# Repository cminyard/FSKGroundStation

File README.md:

# FSKGroundStation

This is a hardware design for a low-cost PacSat satellite ground
station, but it is also general two-way FSK commmunication for the 2
meter and 70 centimeter bands.  It should be possible to build these
in the US $60 range in quantity.  It can do FSK variants ([G]MSK,
[G]FSK, OOK, ASK).  Notably, it cannot do AFSK, the normal 1200bps
communication used over FM radios.

Basically, this is two radios, one for around 136-175MHz, and one for
around 430-450MHz.  Each of these radios is a simplex two-way radio
using a basic ISM radio chip.  It then has an RF power amplifier (PA)
on the TX side to boost the power to the 4-5 watt range and an RF
switch after than to switch between transmit and receive.

The radios are TI CC1125 chips.  These are standard ISM radio chips.
However, those chips are not able to do HDLC or G3RUH 9600 as used in
standard amateur radio communication.  For that, the CC1125 can
send/receive raw FSK data out a GPIO port.  A Lattice ICE40LP1K FPGA
processes the FSK to be able to do HDLC and whitening per G3RUH.

These chips are controlled by a TI CC27x5 processor over SPI.  Also,
this is designed to have enough capability to run as a stand-alone
application, like for a balloon, fox, control device, or something of
that nature.

## Host Communication

Communication with the host is through a MSPM0G5187 processor that has
USB.  It has a SPI connection to the main processor.

There is also a 2.4GHz radio on the CC27x5 processor, so a bluetooth
connection could be done.

## RF Connections

RF input/output is through SMA connectors on the end of the board.
One connector is for 2 meters only, one is for 70cm only, and one has
a diplexer on it and can be used with a dual-band antenna.  You lose
about 1dB in the diplexer, so it's slightly better to have two
antennas.

There are two open-collector (open drain, really) outputs on a 3.5mm
audio-type jack that the CPU can drive for controlling external
amplifiers or for anything else, really.

Note that you really can't transmit on both bands at the same time.
Power draw would go somewhat above 4A and heat dissipation would be a
problem.  If you have a power source that can supply that it might be
ok, but it's pushing things on the heat side.

## Powering the Board

You can use either of the two USB connectors on the board to supply
power.  To use the host connector (J3), install the jumper on J8.  A
second USB connector J10 is a power-only USB connector that can be
used to power the board if the host connection cannot supply enough
current.  To use that install the J11 jumper.

There is also J25, a standard 6.0mm OD 2.5mm ID barrel connector on
the board, center pin is +5V and the outside is ground, as usual.  You
must remove the other power jumpers (J8 and J11) to use this.

All power connectors must supply at least 3A for transmit.

## Clocks

The MSPM0G5187 has a 32.768kHz clock with enough precision to handle
the USB connection.  In addition, it's internal oscillator has a high
precision resistor, so it should be good.

The 32.768kHz oscillator is output and send to the CC27x5 processor.
The CC27x5 processor has it's own 48MHz oscillator with 20ppm
precision.

The MSPM0G5187 also outputs a basic clock that is used to clock the
FPGA.

The CC1125 chips each have their own 40MHz 20ppm TXCO.

## Heat Dissipation and Measurement

The PAs produce a lot of heat.  At full power they will be dissipating
around 4 watts.  The heat mostly comes out through the bottom of the
board on a 2.5mm square copper pad under each PA.

There are a bunch of vias on the edge of the board and three
unobstructed ground planes between these vias and the PAs.  With edge
plating, this should be able to move heat from the ground planes into
the chassis from the edge.  This is experimental.

In case the edge vias and plating don't work, the 2.5mm square copper
pad under the PAs is left bare.  That way a thermally conductive pad
or a heat sink can be put on that to move heat away.

There are two thermsistors on the board, one mounted by each PA, for
measuring temperature.

## Design Variants

Lots of things can be removed if not required, which will decrease the
price and allow slight performance improvements in some cases:

* The 3.5mm external PA control jack and associated circuits can be
  removed if not necessary.

* PacSat satellites transmit on 70cm and receive on 2m, so the ground
  station for that really only has to transmit on 2m and receive on
  70cm.  The 70cm transmit circuits could be removed and the 2m
  receive circuits could be removed.  That means you can remove the RF
  switches on the, gaining about 1dB.  That, of course, makes the
  board less flexible for other purposes.
  
* The diplexer and connector can be removed if not needed.

* If only the diplexer is used, the TX and RX connectors can be removed.

* The radios can be modified to different bands up to the capabilities
  of the various parts.  The limiting factor is the bands supported by
  the radios (TI CC1312R and CC1125 chips) and the capabilities of the
  PA (Guerrilla RF GRF5604, 100-600MHz).

* The power connectors that aren't used can be removed.

## A Box

This was designed to go into a 100mm x 88mm box like:

    JIUWU Surface Drawing Split Aluminum Enclosure Project Box
	Electronic Enclosure Case for PCB Board DIY, 88x38x100mm (WHL),
	Black

on Amazon.  The actual board dimensions are 83mm x 100mm, it should
slide into the slots in the chassis, which is supposed to be 84mm
wide.

## TODO list

* Figure out how to handle heat from the PAs.

  * Screw mount on the bottom.  This would probably require putting
    the external connectors on the bottom of the board to give space
    in a box.  It would also require ventilation of some type and
    maybe a fan.
	
  * Connect a heat transfer device to the box surface.  This would
    require mounting in a box.  If you use the box referenced above,
    there is a 5.2mm gap between the bottom of the circuit board and the
    inside of the box.  I'm not sure how to conduct the head, though.

  * Wurth has some "Graphite Foam Gaskets" that have high thermal
    conductivity and are not electrically conductive, from what I can
    tell (1KV/mm dialectric strength), and not too expensive.  Laird
    has "Thermal Transfer Gaskets," which look similar.  Also
    Bergquist thermally conductive gap pads.  You could put that
    between the PA pad and the chassis.  I can't find one that's the
    right height, though, it needs to be 5.2mm.  Maybe it can be cut?
    The custom make them, but that would be expensive.

  * It would be possible to use 2oz copper on the inner and/or outer
    layers.  This will conduct a lot more heat, but limits the board
    stacks that can be used and requires some impedance adjustments.

  * The edges of the board could be plated, allowing heat transfer out
    of the edges of the board into the chassis.

* The 2m connection to the CC1312R is actually for 169MHz.  A proper
  design for 145MHz needs to be found, or it will need to be tweaked.

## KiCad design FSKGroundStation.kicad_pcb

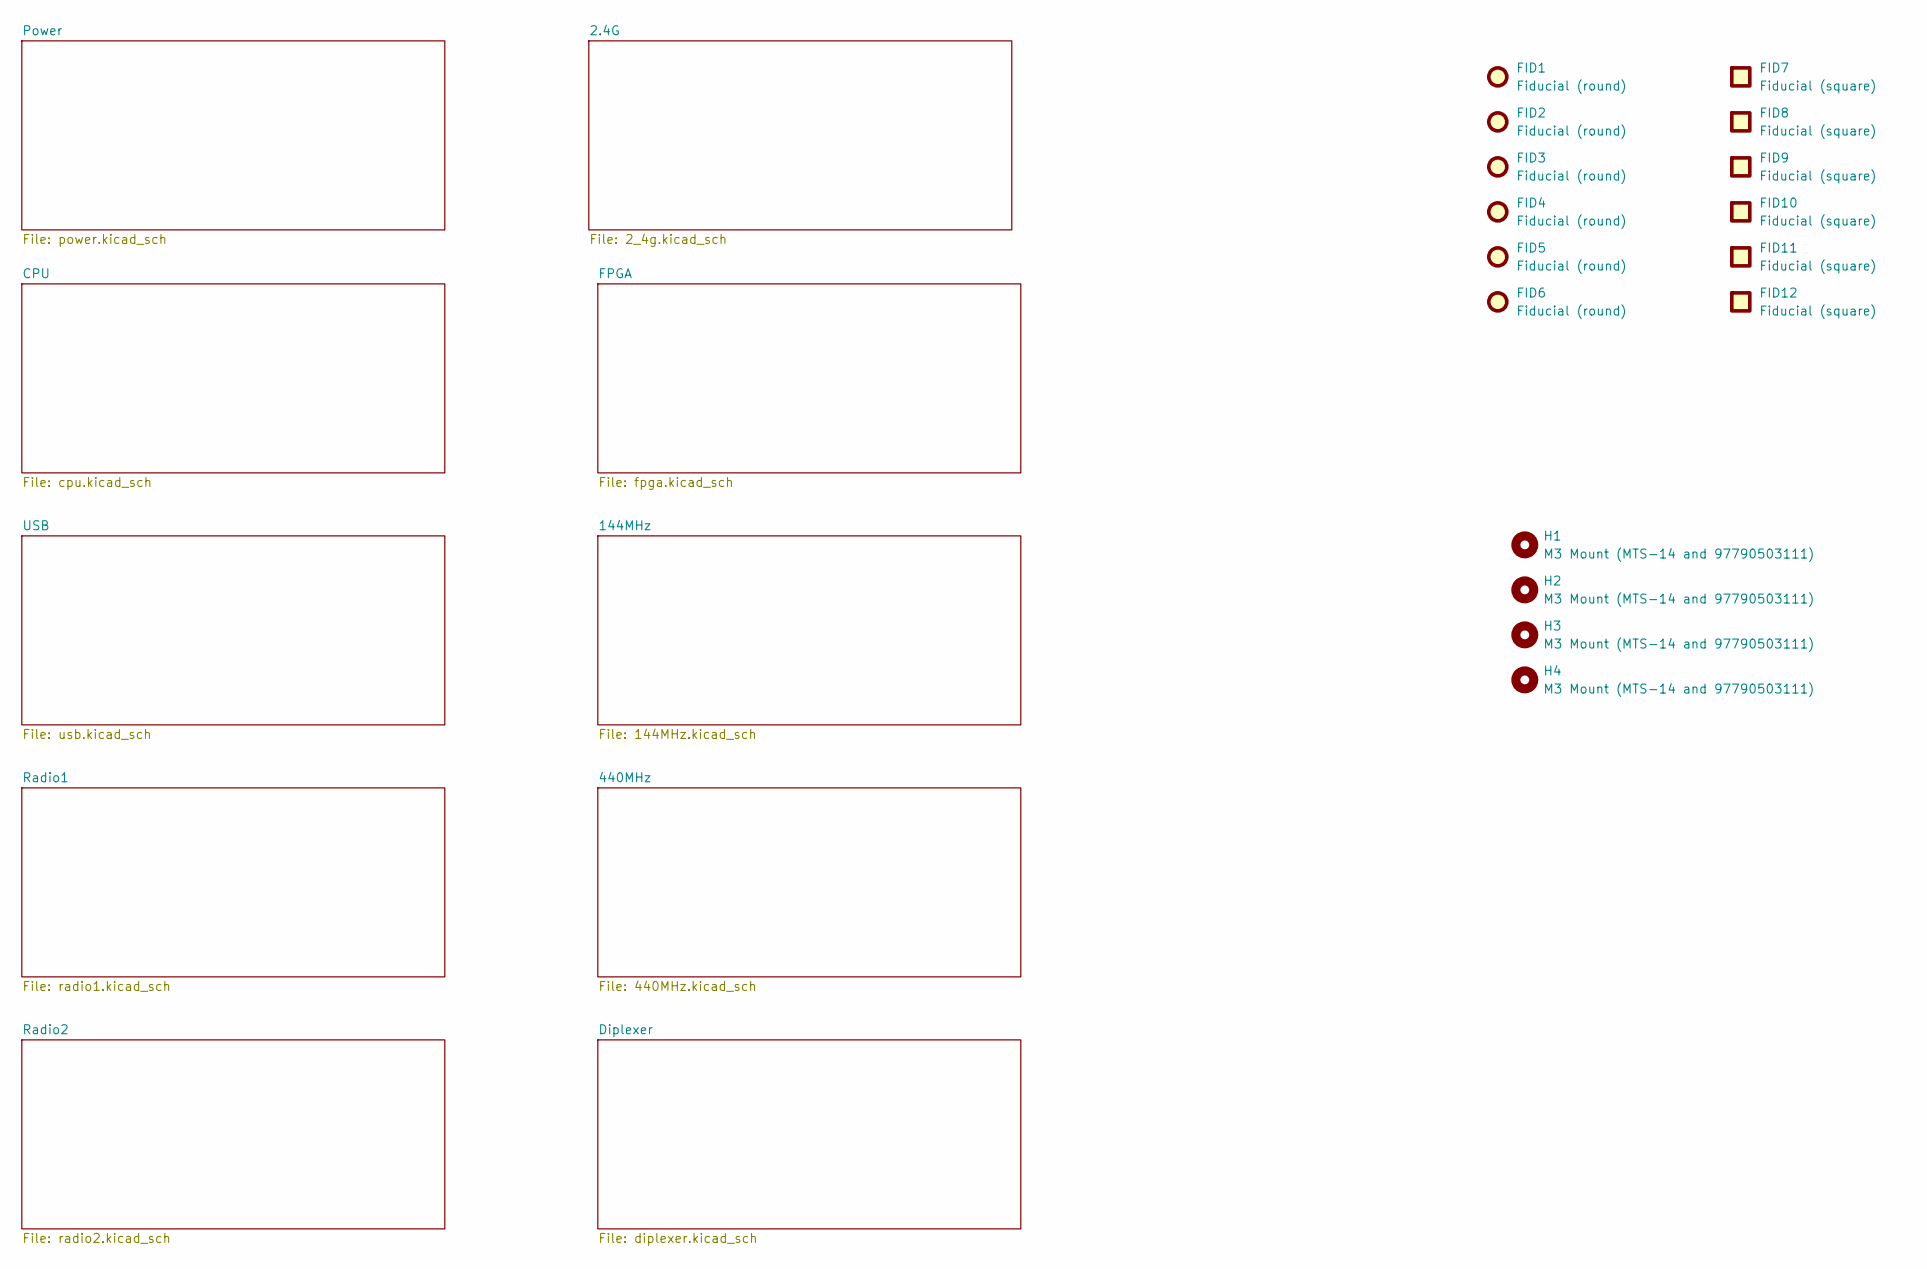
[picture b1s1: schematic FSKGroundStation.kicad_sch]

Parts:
FID1, FID2, FID3, FID4, FID5, FID6: Fiducial (round); Fiducial_1mm_Mask2mm
FID7, FID8, FID9, FID10, FID11, FID12: Fiducial (square); Fiducial_Square_1mm_Mask2mm
H1, H2, H3, H4: M3 Mount (MTS-14 and 97790503111); MountingHole_3.2mm_M3

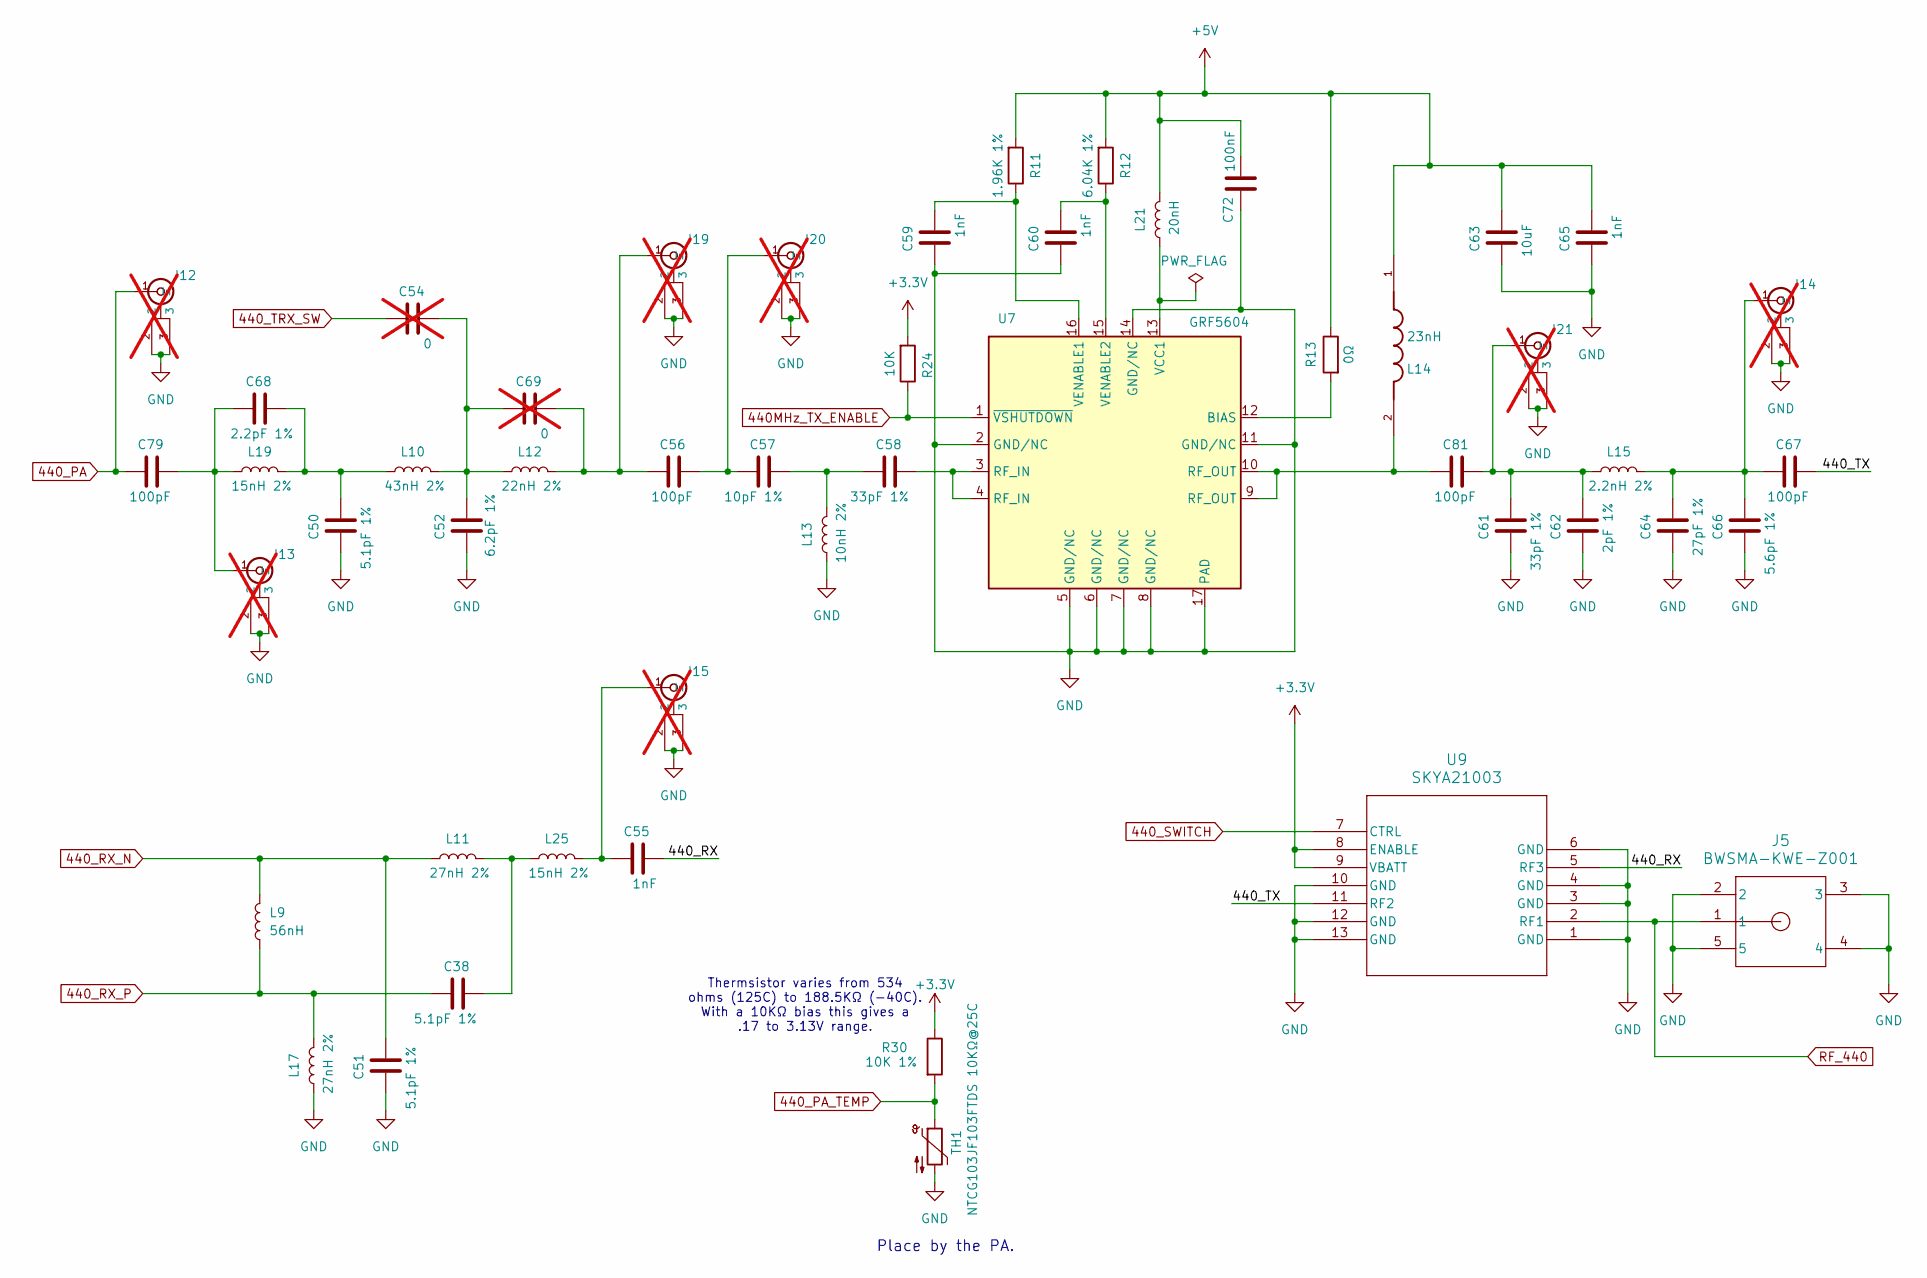
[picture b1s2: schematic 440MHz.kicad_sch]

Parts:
C38, C50, C51: 5.1pF 1%; C_0402_1005Metric_Pad0.74x0.62mm_HandSolder
C52: 6.2pF 1%; C_0402_1005Metric_Pad0.74x0.62mm_HandSolder
C54, C69: 0; C_0402_1005Metric_Pad0.74x0.62mm_HandSolder; not fitted
C55, C59, C60, C65: 1nF; C_0402_1005Metric_Pad0.74x0.62mm_HandSolder
C56, C67, C79, C81: 100pF; C_0402_1005Metric_Pad0.74x0.62mm_HandSolder
C57: 10pF 1%; C_0402_1005Metric_Pad0.74x0.62mm_HandSolder
C58, C61: 33pF 1%; C_0402_1005Metric_Pad0.74x0.62mm_HandSolder
C62: 2pF 1%; C_0402_1005Metric_Pad0.74x0.62mm_HandSolder
C63: 10uF; C_1206_3216Metric_Pad1.33x1.80mm_HandSolder
C64: 27pF 1%; C_0402_1005Metric_Pad0.74x0.62mm_HandSolder
C66: 5.6pF 1%; C_0402_1005Metric_Pad0.74x0.62mm_HandSolder
C68: 2.2pF 1%; C_0402_1005Metric_Pad0.74x0.62mm_HandSolder
C72: 100nF; C_0402_1005Metric_Pad0.74x0.62mm_HandSolder
J5: BWSMA-KWE-Z001; CONN_BWSMA-KWE-Z001_BAT
J12, J13, J14, J15, J19, J20, J21: CONN1_CONUFL_TEC; not fitted
L9: 56nH; L_0603_1608Metric_Pad1.05x0.95mm_HandSolder
L10: 43nH 2%; L_0402_1005Metric_Pad0.77x0.64mm_HandSolder
L11, L17: 27nH 2%; L_0402_1005Metric_Pad0.77x0.64mm_HandSolder
L12: 22nH 2%; L_0402_1005Metric_Pad0.77x0.64mm_HandSolder
L13: 10nH 2%; L_0402_1005Metric_Pad0.77x0.64mm_HandSolder
L14: 23nH; IND_0908SQ-23NJLC; PARTREV 12/21/22
L15: 2.2nH 2%; L_0402_1005Metric_Pad0.77x0.64mm_HandSolder
L19, L25: 15nH 2%; L_0402_1005Metric_Pad0.77x0.64mm_HandSolder
L21: 20nH; L_0402_1005Metric_Pad0.77x0.64mm_HandSolder
R11: 1.96K 1%; R_0402_1005Metric
R12: 6.04K 1%; R_0402_1005Metric
R13: 0Ω; R_0402_1005Metric
R24: 10K; R_0402_1005Metric
R30: 10K 1%; R_0402_1005Metric_Pad0.72x0.64mm_HandSolder
TH1: NTCG103JF103FTDS 10KΩ@25C; R_0402_1005Metric
U7: GRF5604; QFN-16-1EP_3x3mm_P0.5mm_EP1.7x1.7mm
U9: SKYA21003; QFN12_SKYA21003_SKY

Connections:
440MHz_TX_ENABLE: R24.1, U7.1 (~VSHUTDOWN); also elsewhere on the board
440_PA: C79.1, J12.1 (In); also elsewhere on the board
440_PA_TEMP: R30.2, TH1.1; also elsewhere on the board
440_RX_N: C51.2, L9.2, L11.1; also elsewhere on the board
440_RX_P: C38.1, L9.1, L17.2; also elsewhere on the board
440_SWITCH: U9.7 (CTRL); also elsewhere on the board
440_TRX_SW: C54.1; also elsewhere on the board
+3.3V: R24.2, R30.1, U9.8 (ENABLE), U9.9 (VBATT); also elsewhere on the board
+5V: C63.2, C65.2, C72.2, L14.1, L21.2, R11.2, R12.2, R13.1; also elsewhere on the board
/440MHz/440_RX: C55.2, U9.5 (RF3)
/440MHz/440_TX: C67.2, U9.11 (RF2)
GND: C50.1, C51.1, C52.1, C59.1, C60.1, C61.1, C62.1, C63.1, C64.1, C65.1, C66.1, C72.1, J5.2, J5.3, J5.4, J5.5, J12.2, J12.3, J13.2, J13.3, J14.2, J14.3, J15.2, J15.3, J19.2, J19.3, J20.2, J20.3, J21.2, J21.3, L13.1, L17.1, TH1.2, U7.2 (GND/NC), U7.5 (GND/NC), U7.6 (GND/NC), U7.7 (GND/NC), U7.8 (GND/NC), U7.11 (GND/NC), U7.14 (GND/NC), U7.17 (PAD), U9.1 (GND), U9.3 (GND), U9.4 (GND), U9.6 (GND), U9.10 (GND), U9.12 (GND), U9.13 (GND); also elsewhere on the board
unnamed: C38.2, L11.2, L25.1
unnamed: C50.2, C68.2, L10.1, L19.2
unnamed: C52.2, C54.2, C69.1, L10.2, L12.1
unnamed: C57.2, C58.1, L13.2
unnamed: C58.2, U7.3 (RF_IN), U7.4 (RF_IN)
unnamed: C81.1, L14.2, U7.9 (RF_OUT), U7.10 (RF_OUT)
unnamed: C68.1, C79.2, J13.1 (In), L19.1
unnamed: C64.2, C66.2, C67.1, J14.1 (In), L15.2
unnamed: C55.1, J15.1 (In), L25.2
unnamed: C56.1, C69.2, J19.1 (In), L12.2
unnamed: C56.2, C57.1, J20.1 (In)
unnamed: C61.2, C62.2, C81.2, J21.1 (In), L15.1
unnamed: R13.2, U7.12 (BIAS)
unnamed: L21.1, U7.13 (VCC1)
unnamed: C59.2, R11.1, U7.16 (VENABLE1)
unnamed: C60.2, R12.1, U7.15 (VENABLE2)
RF_440: J5.1, U9.2 (RF1); also elsewhere on the board

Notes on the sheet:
Thermsistor varies from 534 ohms (125C) to 188.5KΩ (-40C). With a 10KΩ bias this gives a .17 to 3.13V range.
Place by the PA.

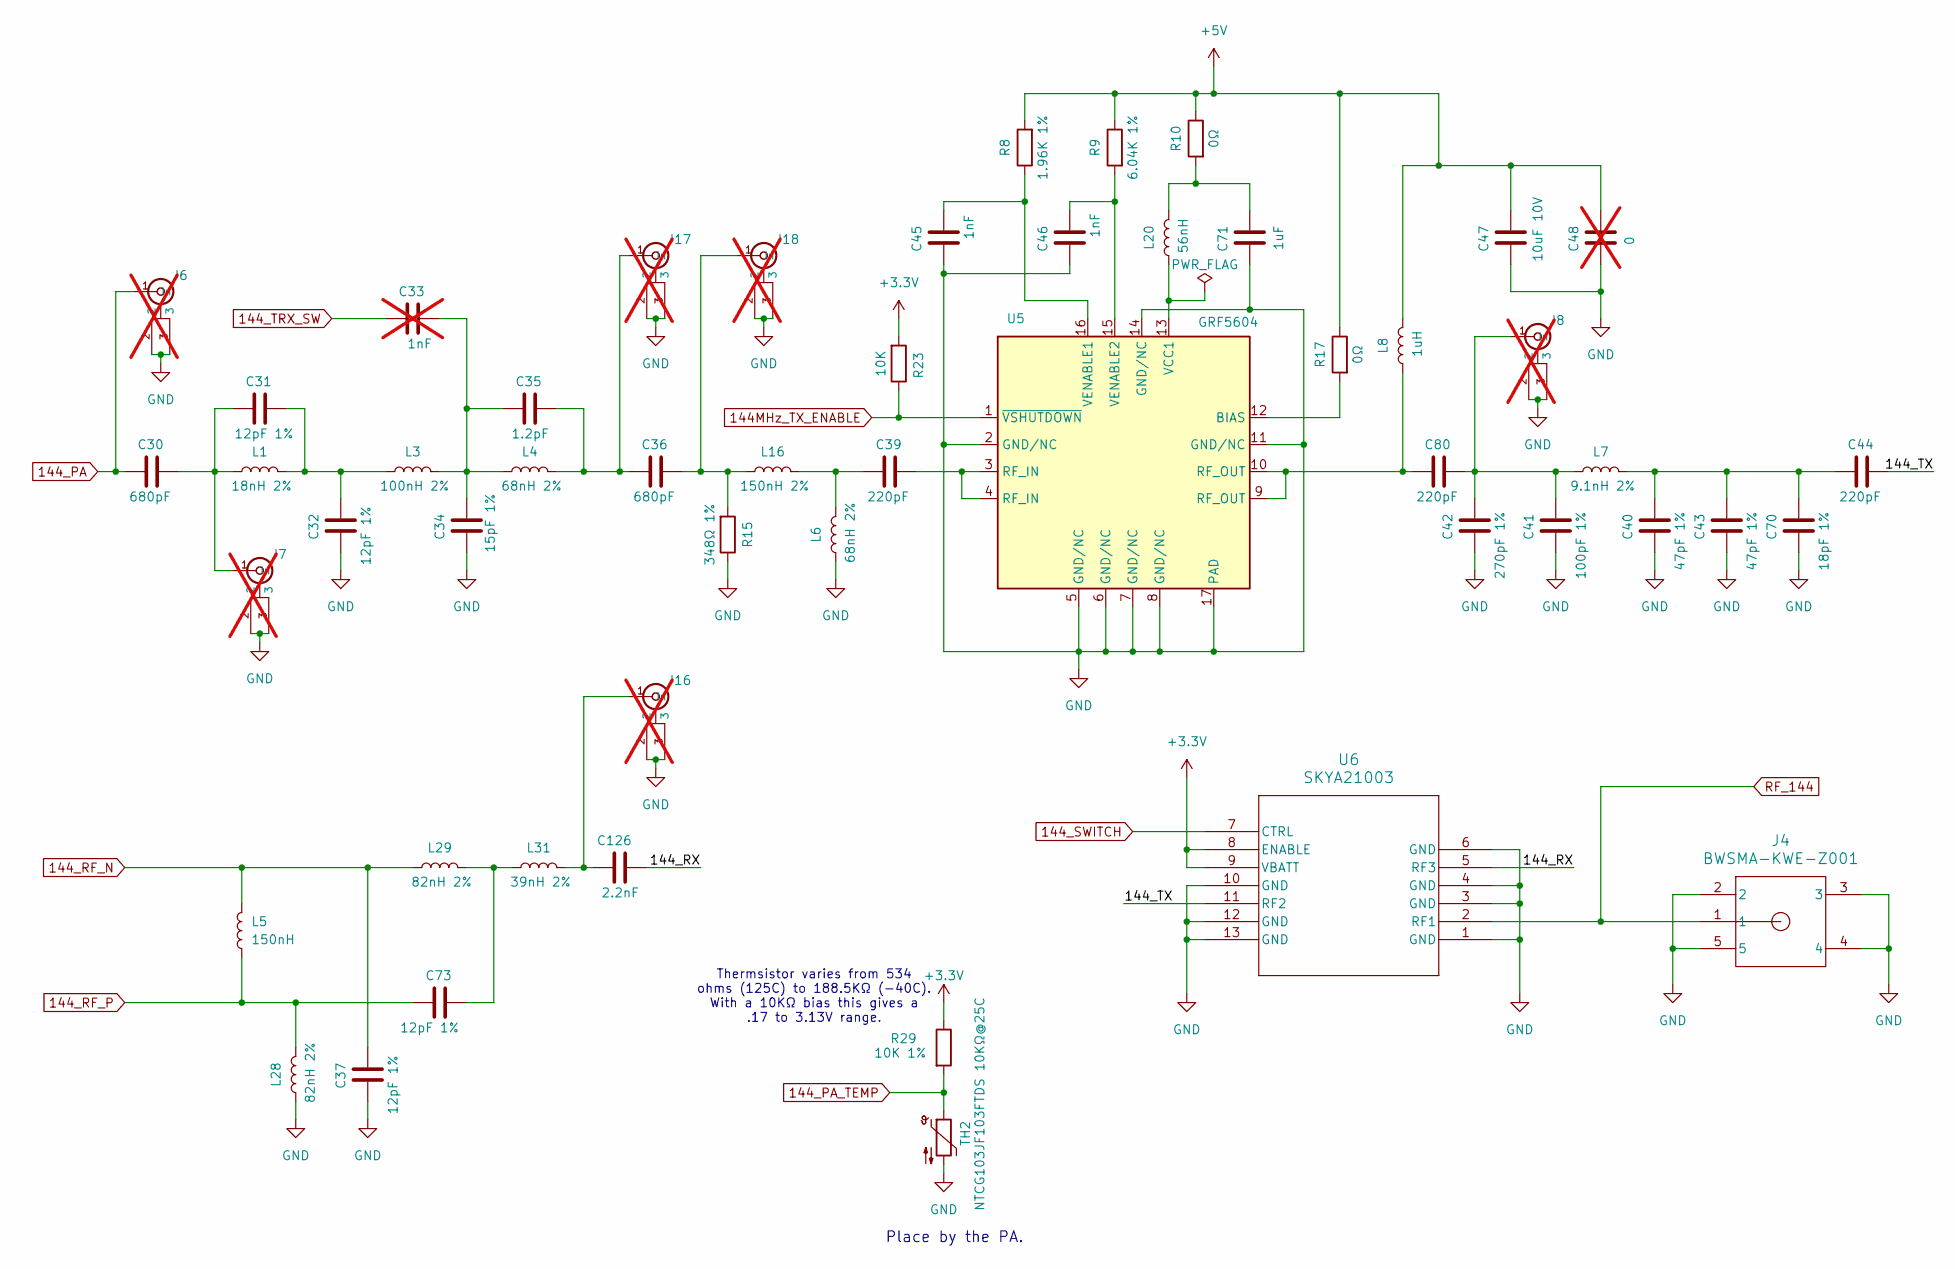
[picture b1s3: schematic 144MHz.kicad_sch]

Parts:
C30, C36: 680pF; C_0402_1005Metric_Pad0.74x0.62mm_HandSolder
C31, C32, C37, C73: 12pF 1%; C_0402_1005Metric_Pad0.74x0.62mm_HandSolder
C33: 1nF; C_0402_1005Metric_Pad0.74x0.62mm_HandSolder; not fitted
C34: 15pF 1%; C_0402_1005Metric_Pad0.74x0.62mm_HandSolder
C35: 1.2pF; C_0402_1005Metric_Pad0.74x0.62mm_HandSolder
C39, C44, C80: 220pF; C_0402_1005Metric_Pad0.74x0.62mm_HandSolder
C40, C43: 47pF 1%; C_0402_1005Metric_Pad0.74x0.62mm_HandSolder
C41: 100pF 1%; C_0402_1005Metric_Pad0.74x0.62mm_HandSolder
C42: 270pF 1%; C_0402_1005Metric_Pad0.74x0.62mm_HandSolder
C45, C46: 1nF; C_0402_1005Metric_Pad0.74x0.62mm_HandSolder
C47: 10uF 10V; C_1206_3216Metric_Pad1.33x1.80mm_HandSolder
C48: 0; C_0402_1005Metric_Pad0.74x0.62mm_HandSolder; not fitted
C70: 18pF 1%; C_0402_1005Metric_Pad0.74x0.62mm_HandSolder
C71: 1uF; C_0603_1608Metric_Pad1.08x0.95mm_HandSolder
C126: 2.2nF; C_0402_1005Metric_Pad0.74x0.62mm_HandSolder
J4: BWSMA-KWE-Z001; CONN_BWSMA-KWE-Z001_BAT
J6, J7, J8, J16, J17, J18: CONN1_CONUFL_TEC; not fitted
L1: 18nH 2%; L_0402_1005Metric_Pad0.77x0.64mm_HandSolder
L3: 100nH 2%; L_0603_1608Metric_Pad1.05x0.95mm_HandSolder
L4, L6: 68nH 2%; L_0603_1608Metric_Pad1.05x0.95mm_HandSolder
L5: 150nH; L_0805_2012Metric_Pad1.05x1.20mm_HandSolder
L7: 9.1nH 2%; L_0402_1005Metric_Pad0.77x0.64mm_HandSolder
L8: 1uH; L_1008_2520Metric_Pad1.43x2.20mm_HandSolder
L16: 150nH 2%; L_0805_2012Metric_Pad1.05x1.20mm_HandSolder
L20: 56nH; L_0603_1608Metric_Pad1.05x0.95mm_HandSolder
L28, L29: 82nH 2%; L_0603_1608Metric_Pad1.05x0.95mm_HandSolder
L31: 39nH 2%; L_0402_1005Metric_Pad0.77x0.64mm_HandSolder
R8: 1.96K 1%; R_0402_1005Metric
R9: 6.04K 1%; R_0402_1005Metric
R10, R17: 0Ω; R_0402_1005Metric
R15: 348Ω 1%; R_0402_1005Metric
R23: 10K; R_0402_1005Metric
R29: 10K 1%; R_0402_1005Metric_Pad0.72x0.64mm_HandSolder
TH2: NTCG103JF103FTDS 10KΩ@25C; R_0402_1005Metric
U5: GRF5604; QFN-16-1EP_3x3mm_P0.5mm_EP1.7x1.7mm
U6: SKYA21003; QFN12_SKYA21003_SKY

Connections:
144MHz_TX_ENABLE: R23.1, U5.1 (~VSHUTDOWN); also elsewhere on the board
144_PA: C30.1, J6.1 (In); also elsewhere on the board
144_PA_TEMP: R29.2, TH2.1; also elsewhere on the board
144_RF_N: C37.2, L5.2, L29.1; also elsewhere on the board
144_RF_P: C73.1, L5.1, L28.2; also elsewhere on the board
144_SWITCH: U6.7 (CTRL); also elsewhere on the board
144_TRX_SW: C33.1; also elsewhere on the board
+3.3V: R23.2, R29.1, U6.8 (ENABLE), U6.9 (VBATT); also elsewhere on the board
+5V: C47.2, C48.2, L8.2, R8.2, R9.1, R10.1, R17.1; also elsewhere on the board
/144MHz/144_RX: C126.2, U6.5 (RF3)
/144MHz/144_TX: C44.2, U6.11 (RF2)
GND: C32.1, C34.1, C37.1, C40.1, C41.1, C42.1, C43.1, C45.1, C46.1, C47.1, C48.1, C70.1, C71.1, J4.2, J4.3, J4.4, J4.5, J6.2, J6.3, J7.2, J7.3, J8.2, J8.3, J16.2, J16.3, J17.2, J17.3, J18.2, J18.3, L6.1, L28.1, R15.1, TH2.2, U5.2 (GND/NC), U5.5 (GND/NC), U5.6 (GND/NC), U5.7 (GND/NC), U5.8 (GND/NC), U5.11 (GND/NC), U5.14 (GND/NC), U5.17 (PAD), U6.1 (GND), U6.3 (GND), U6.4 (GND), U6.6 (GND), U6.10 (GND), U6.12 (GND), U6.13 (GND); also elsewhere on the board
unnamed: C31.2, C32.2, L1.2, L3.1
unnamed: C33.2, C34.2, C35.1, L3.2, L4.1
unnamed: C39.1, L6.2, L16.2
unnamed: C39.2, U5.3 (RF_IN), U5.4 (RF_IN)
unnamed: C40.2, C43.2, C44.1, C70.2, L7.2
unnamed: C71.2, L20.2, R10.2
unnamed: C73.2, L29.2, L31.1
unnamed: C80.1, L8.1, U5.9 (RF_OUT), U5.10 (RF_OUT)
unnamed: C30.2, C31.1, J7.1 (In), L1.1
unnamed: C41.2, C42.2, C80.2, J8.1 (In), L7.1
unnamed: C126.1, J16.1 (In), L31.2
unnamed: C35.2, C36.1, J17.1 (In), L4.2
unnamed: C36.2, J18.1 (In), L16.1, R15.2
unnamed: R17.2, U5.12 (BIAS)
unnamed: L20.1, U5.13 (VCC1)
unnamed: C45.2, R8.1, U5.16 (VENABLE1)
unnamed: C46.2, R9.2, U5.15 (VENABLE2)
RF_144: J4.1, U6.2 (RF1); also elsewhere on the board

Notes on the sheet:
Thermsistor varies from 534 ohms (125C) to 188.5KΩ (-40C). With a 10KΩ bias this gives a .17 to 3.13V range.
Place by the PA.

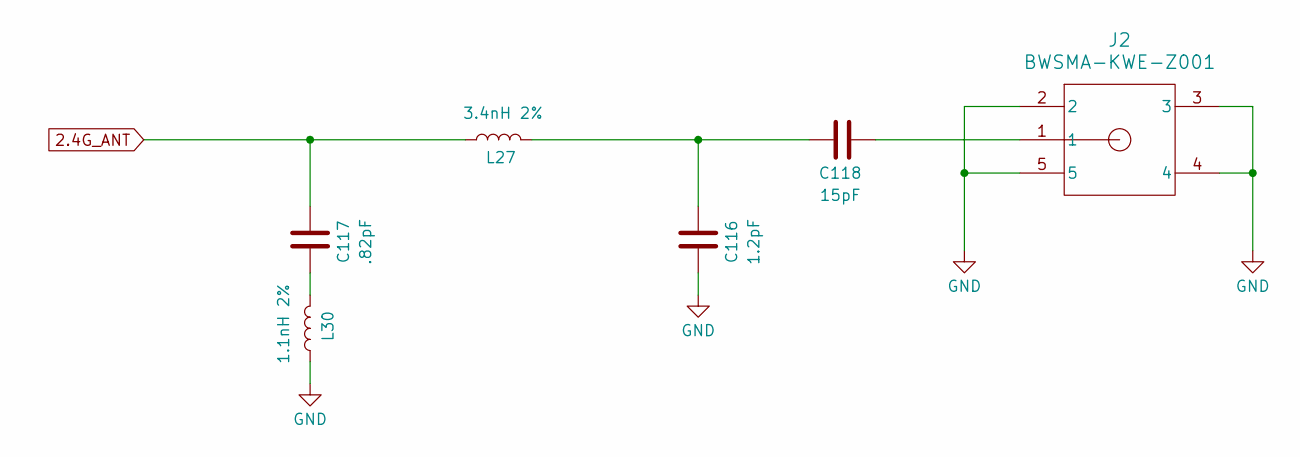
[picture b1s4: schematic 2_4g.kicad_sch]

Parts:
C116: 1.2pF; C_0402_1005Metric_Pad0.74x0.62mm_HandSolder
C117: .82pF; C_0402_1005Metric_Pad0.74x0.62mm_HandSolder
C118: 15pF; C_0402_1005Metric_Pad0.74x0.62mm_HandSolder
J2: BWSMA-KWE-Z001; CONN_BWSMA-KWE-Z001_BAT
L27: 3.4nH 2%; L_0402_1005Metric_Pad0.77x0.64mm_HandSolder
L30: 1.1nH 2%; L_0402_1005Metric_Pad0.77x0.64mm_HandSolder

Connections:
2.4G_ANT: C117.2, L27.1; also elsewhere on the board
GND: C116.1, J2.2, J2.3, J2.4, J2.5, L30.1; also elsewhere on the board
unnamed: C116.2, C118.1, L27.2
unnamed: C117.1, L30.2
unnamed: C118.2, J2.1

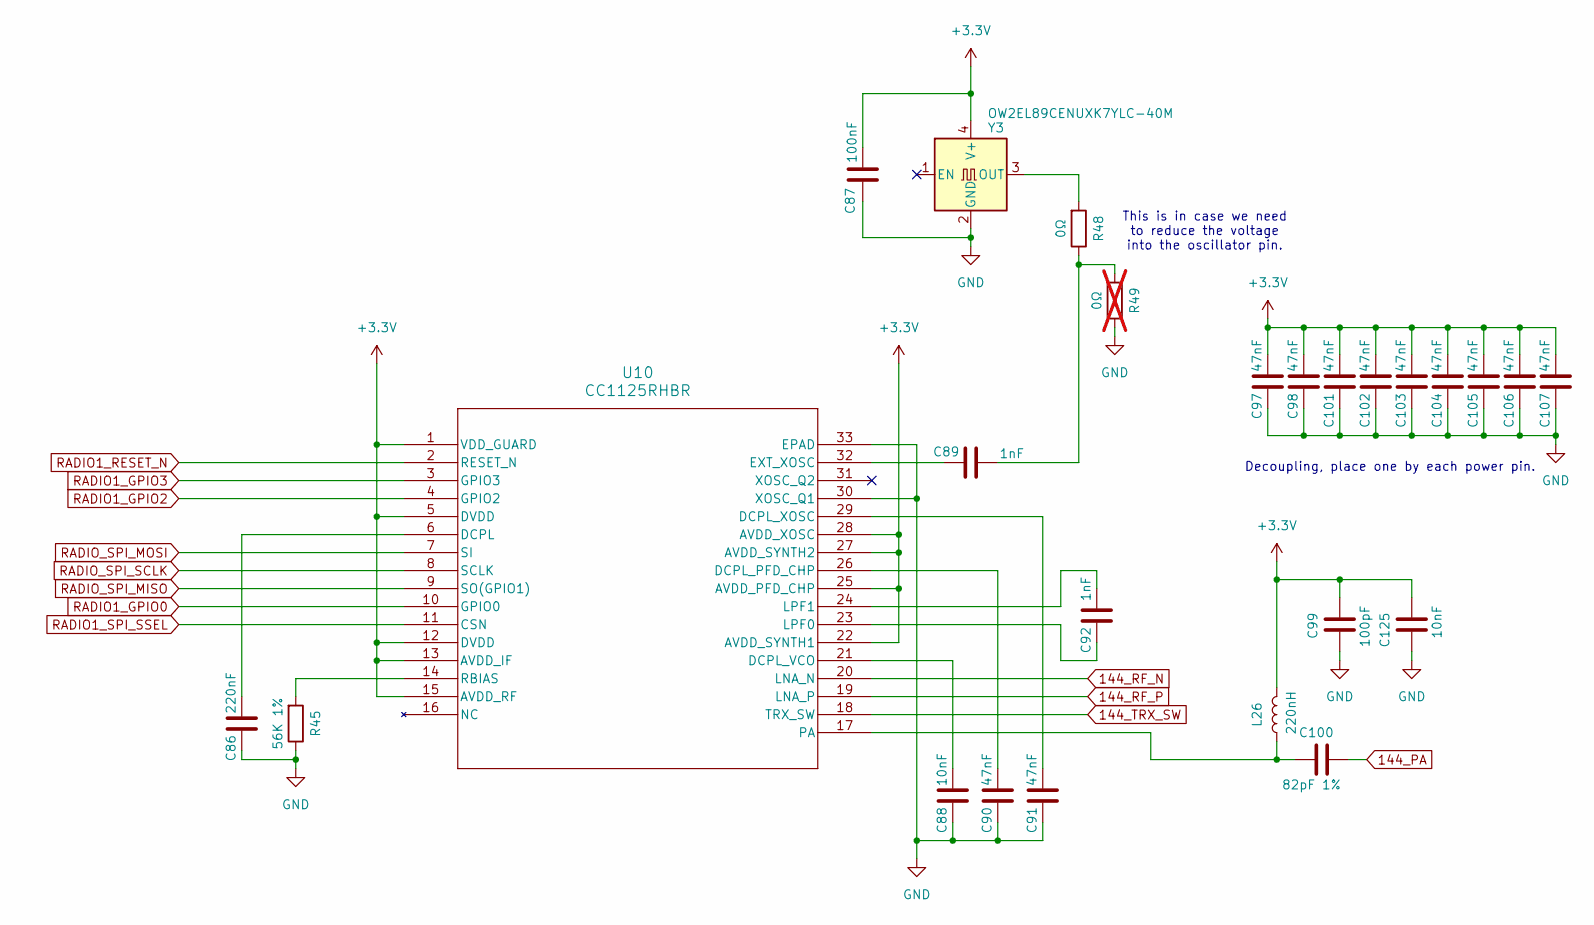
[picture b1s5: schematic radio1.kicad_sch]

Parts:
C86: 220nF; C_0402_1005Metric_Pad0.74x0.62mm_HandSolder
C87: 100nF; C_0402_1005Metric_Pad0.74x0.62mm_HandSolder
C88, C125: 10nF; C_0402_1005Metric_Pad0.74x0.62mm_HandSolder
C89, C92: 1nF; C_0402_1005Metric_Pad0.74x0.62mm_HandSolder
C90, C91, C97, C98, C101, C102, C103, C104, C105, C106, C107: 47nF; C_0402_1005Metric_Pad0.74x0.62mm_HandSolder
C99: 100pF; C_0402_1005Metric_Pad0.74x0.62mm_HandSolder
C100: 82pF 1%; C_0402_1005Metric_Pad0.74x0.62mm_HandSolder
L26: 220nH; L_0805_2012Metric_Pad1.05x1.20mm_HandSolder
R45: 56K 1%; R_0402_1005Metric
R48: 0Ω; R_0402_1005Metric
R49: 0Ω; R_0402_1005Metric; not fitted
U10: CC1125RHBR; RHB32_3P45X3P45_TEX
Y3: OW2EL89CENUXK7YLC-40M; Oscillator_SMD_SiT_PQFN-4Pin_2.0x1.6mm

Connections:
144_PA: C100.2; also elsewhere on the board
144_RF_N: U10.20 (LNA_N); also elsewhere on the board
144_RF_P: U10.19 (LNA_P); also elsewhere on the board
144_TRX_SW: U10.18 (TRX_SW); also elsewhere on the board
+3.3V: C87.2, C97.2, C98.2, C99.2, C101.2, C102.2, C103.2, C104.2, C105.2, C106.2, C107.2, C125.2, L26.2, U10.1 (VDD_GUARD), U10.5 (DVDD), U10.12 (DVDD), U10.13 (AVDD_IF), U10.15 (AVDD_RF), U10.22 (AVDD_SYNTH1), U10.25 (AVDD_PFD_CHP), U10.27 (AVDD_SYNTH2), U10.28 (AVDD_XOSC), Y3.4 (V+); also elsewhere on the board
GND: C86.1, C87.1, C88.1, C90.1, C91.1, C97.1, C98.1, C99.1, C101.1, C102.1, C103.1, C104.1, C105.1, C106.1, C107.1, C125.1, R45.1, R49.1, U10.30 (XOSC_Q1), U10.33 (EPAD), Y3.2 (GND); also elsewhere on the board
unnamed: C89.2, R48.1, R49.2
unnamed: C86.2, U10.6 (DCPL)
unnamed: C90.2, U10.26 (DCPL_PFD_CHP)
unnamed: C88.2, U10.21 (DCPL_VCO)
unnamed: C91.2, U10.29 (DCPL_XOSC)
unnamed: C89.1, U10.32 (EXT_XOSC)
unnamed: C92.1, U10.23 (LPF0)
unnamed: C92.2, U10.24 (LPF1)
unnamed: C100.1, L26.1, U10.17 (PA)
unnamed: R45.2, U10.14 (RBIAS)
unnamed: R48.2, Y3.3 (OUT)
RADIO1_GPIO0: U10.10 (GPIO0); also elsewhere on the board
RADIO1_GPIO2: U10.4 (GPIO2); also elsewhere on the board
RADIO1_GPIO3: U10.3 (GPIO3); also elsewhere on the board
RADIO1_RESET_N: U10.2 (RESET_N); also elsewhere on the board
RADIO1_SPI_SSEL: U10.11 (CSN); also elsewhere on the board
RADIO_SPI_MISO: U10.9 (SO(GPIO1)); also elsewhere on the board
RADIO_SPI_MOSI: U10.7 (SI); also elsewhere on the board
RADIO_SPI_SCLK: U10.8 (SCLK); also elsewhere on the board

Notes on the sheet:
This is in case we need to reduce the voltage into the oscillator pin.
Decoupling, place one by each power pin.

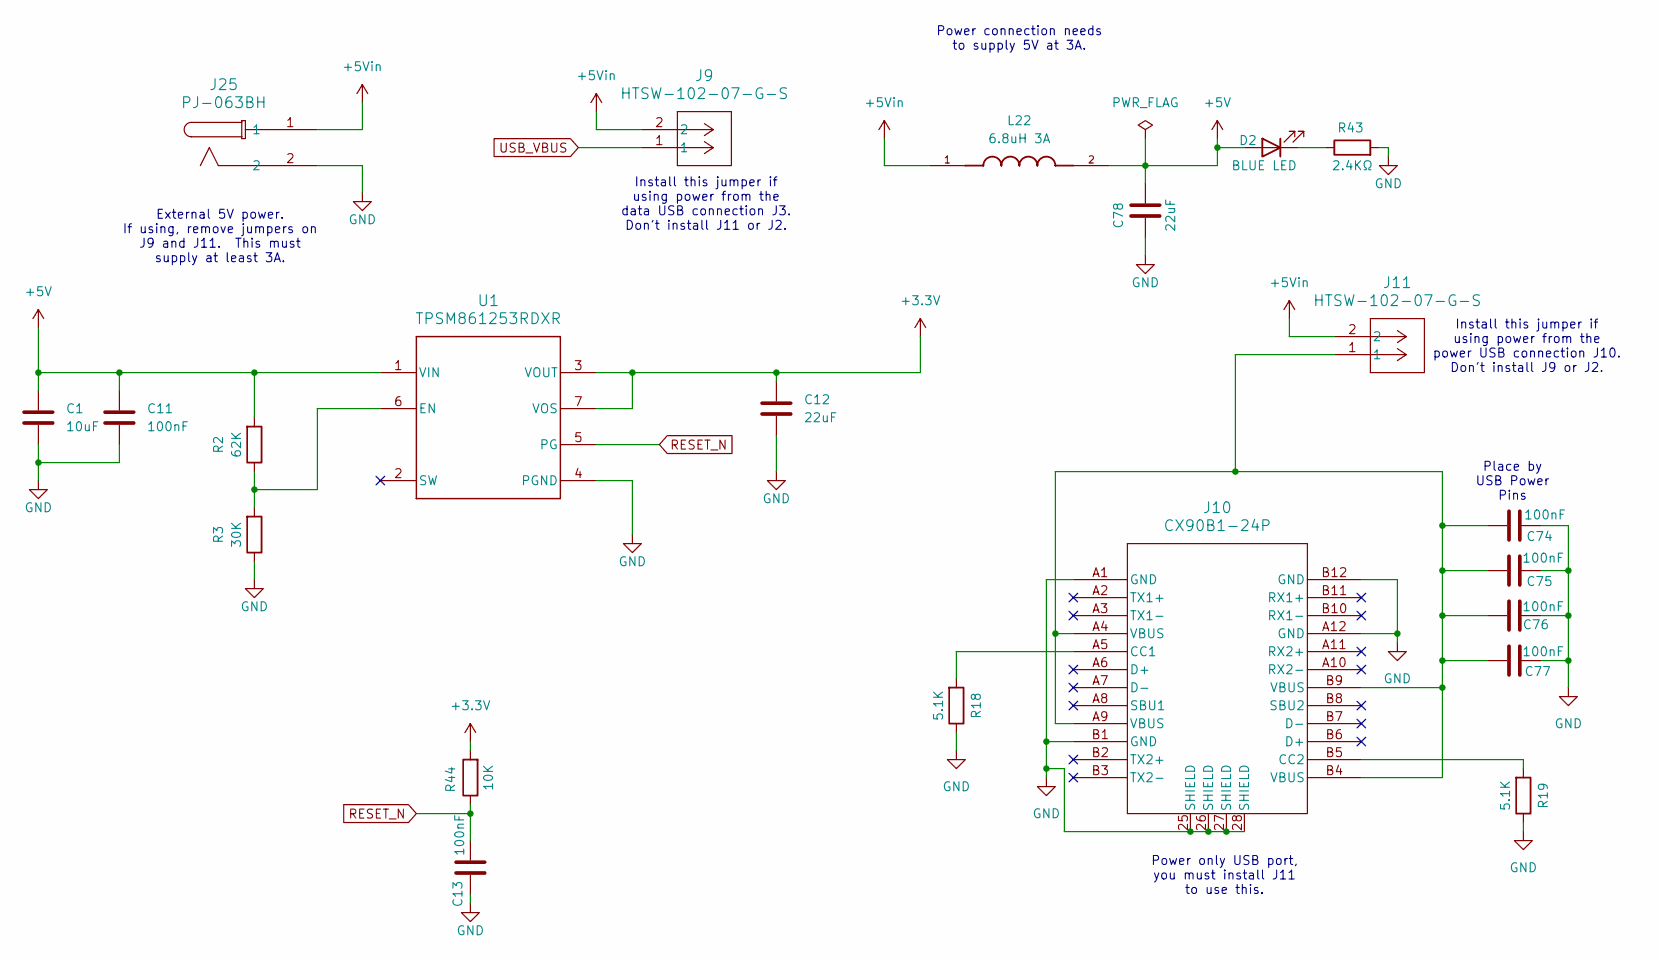
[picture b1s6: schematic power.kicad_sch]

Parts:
C1: 10uF; C_1206_3216Metric_Pad1.33x1.80mm_HandSolder
C11, C13: 100nF; C_0402_1005Metric_Pad0.74x0.62mm_HandSolder
C12, C78: 22uF; C_1206_3216Metric_Pad1.33x1.80mm_HandSolder
C74, C75, C76, C77: 100nF; C_0402_1005Metric
D2: BLUE LED; LED_0603_1608Metric_Pad1.05x0.95mm_HandSolder
J9, J11: HTSW-102-07-G-S; CON2_1X2_TU_TSW
J10: CX90B1-24P; CX90B1-24P_HIR
J25: PJ-063BH; PJ-063BH_CUD
L22: 6.8uH 3A; IND_1255AY-6R8M=P3; PARTREV N/A; DigiKey_Part_Number 490-14063-1-ND
R2: 62K; R_0402_1005Metric
R3: 30K; R_0402_1005Metric
R18, R19: 5.1K; R_0402_1005Metric
R43: 2.4KΩ; R_0603_1608Metric_Pad0.98x0.95mm_HandSolder
R44: 10K; R_0402_1005Metric
U1: TPSM861253RDXR; RDX0007A-MFG

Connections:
+3.3V: C12.1, R44.2, U1.3 (VOUT), U1.7 (VOS); also elsewhere on the board
+5V: C1.1, C11.1, C78.2, D2.2 (A), L22.2, R2.2, U1.1 (VIN); also elsewhere on the board
+5Vin: J9.2, J11.2, J25.1, L22.1
GND: C1.2, C11.2, C12.2, C13.1, C74.2, C75.2, C76.2, C77.2, C78.1, J10.25 (SHIELD), J10.26 (SHIELD), J10.27 (SHIELD), J10.28 (SHIELD), J10.A1 (GND), J10.A12 (GND), J10.B1 (GND), J10.B12 (GND), J25.2, R3.1, R18.1, R19.1, R43.2, U1.4 (PGND); also elsewhere on the board
unnamed: C74.1, C75.1, C76.1, C77.1, J10.A4 (VBUS), J10.A9 (VBUS), J10.B4 (VBUS), J10.B9 (VBUS), J11.1
unnamed: D2.1 (K), R43.1
unnamed: J10.A5 (CC1), R18.2
unnamed: J10.B5 (CC2), R19.2
unnamed: R2.1, R3.2, U1.6 (EN)
RESET_N: C13.2, R44.1, U1.5 (PG); also elsewhere on the board
USB_VBUS: J9.1; also elsewhere on the board

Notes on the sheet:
Power connection needs to supply 5V at 3A.
Power only USB port, you must install J11 to use this.
Install this jumper if using power from the data USB connection J3. Don't install J11 or J2.
Place by USB Power Pins
External 5V power. If using, remove jumpers on J9 and J11. This must supply at least 3A.
Install this jumper if using power from the power USB connection J10. Don't install J9 or J2.
